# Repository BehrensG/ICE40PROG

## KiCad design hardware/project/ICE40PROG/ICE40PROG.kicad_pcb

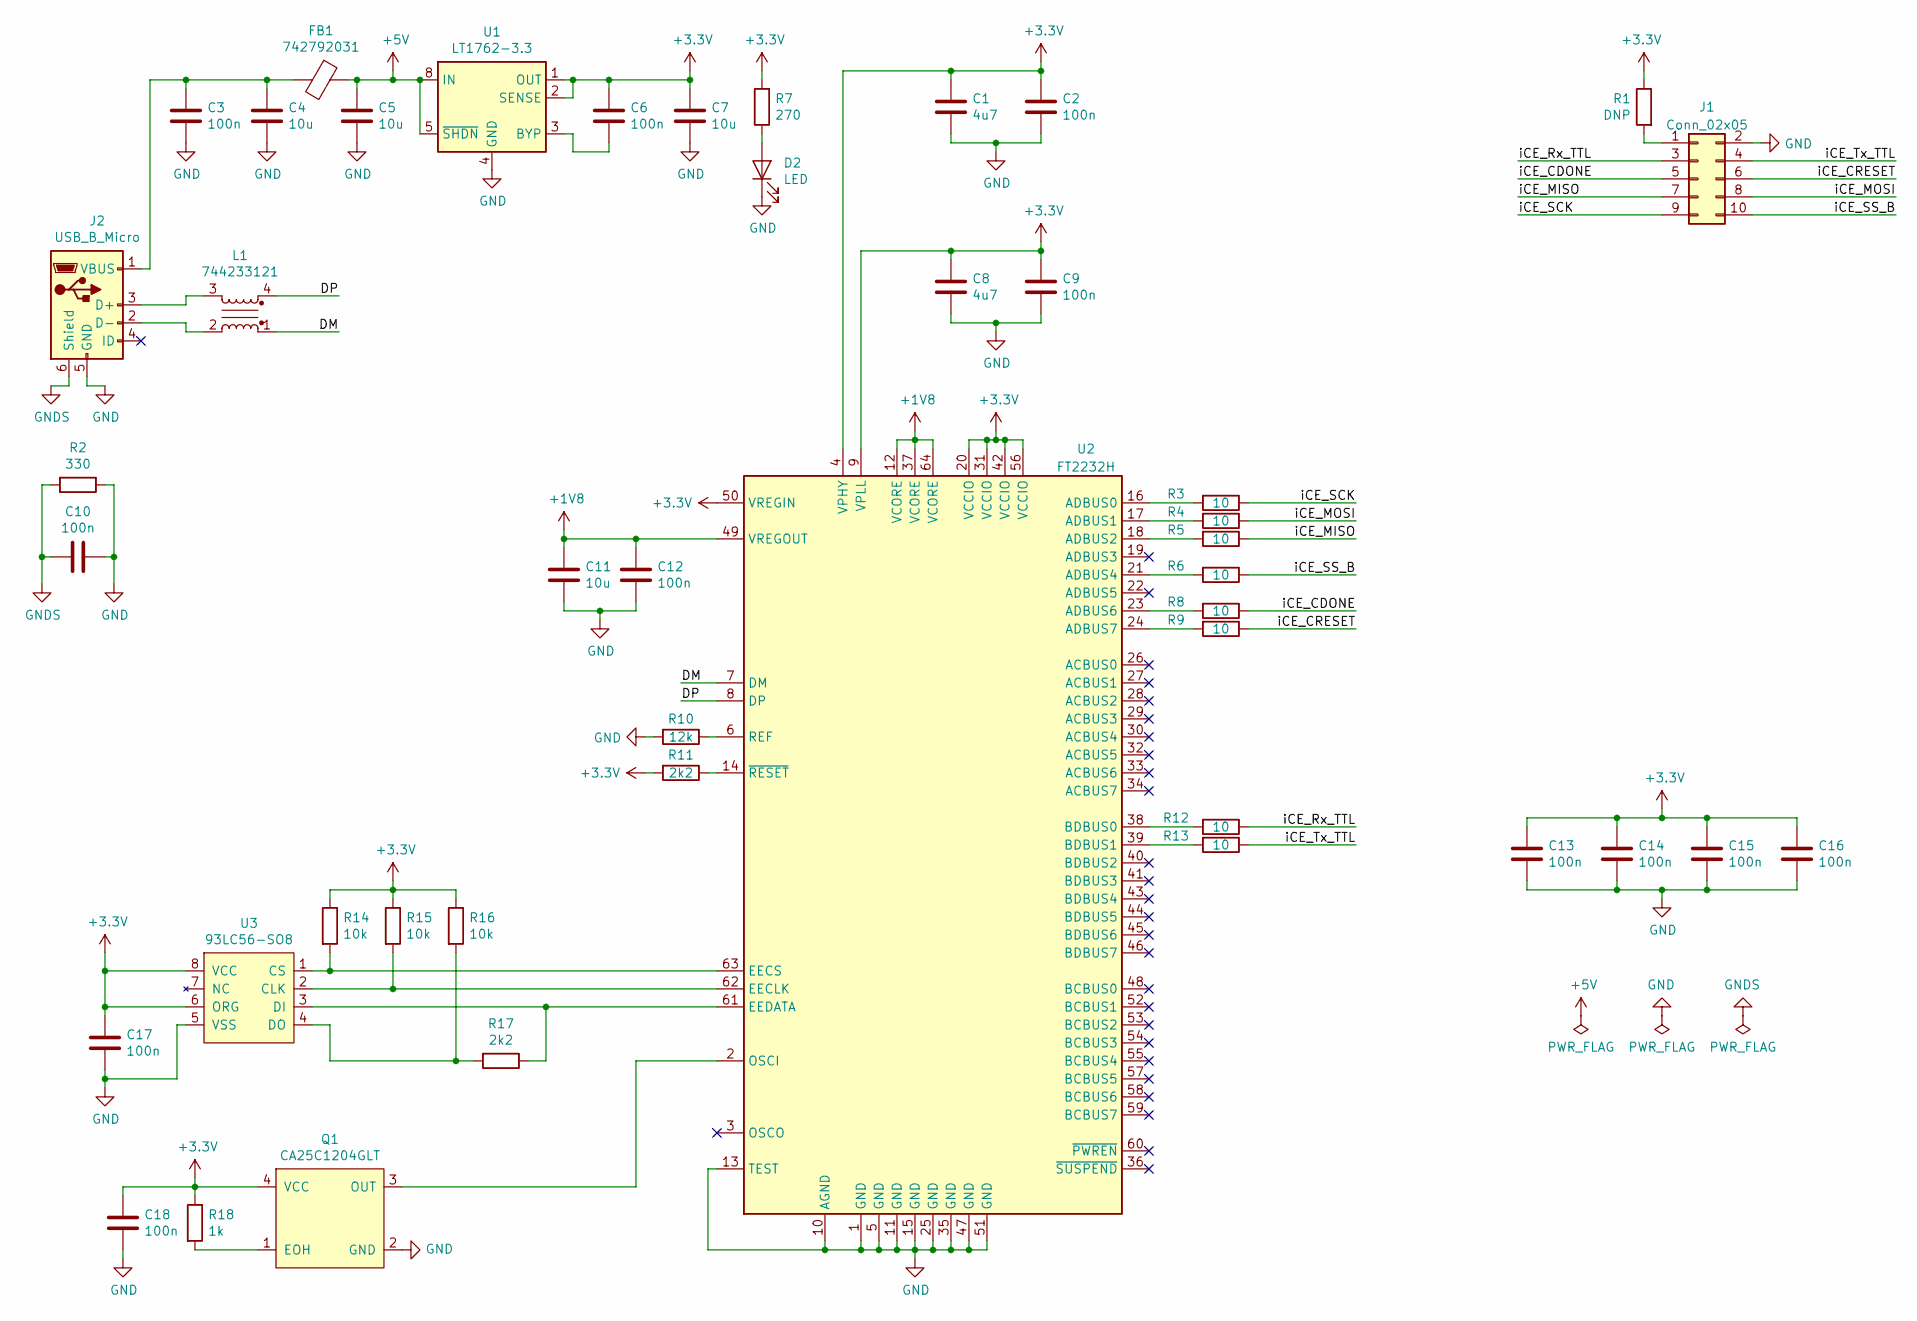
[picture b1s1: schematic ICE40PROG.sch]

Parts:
C1, C8: 4u7; C_0603_1608Metric_Pad1.05x0.95mm_HandSolder
C2, C3, C6, C9, C10, C12, C13, C14, C15, C16, C17, C18: 100n; C_0603_1608Metric_Pad1.05x0.95mm_HandSolder
C4, C5, C7, C11: 10u; C_0603_1608Metric_Pad1.05x0.95mm_HandSolder
D2: LED; LED_0603_1608Metric_Pad1.05x0.95mm_HandSolder
FB1: 742792031; R_0805_2012Metric_Pad1.15x1.40mm_HandSolder
J1: Conn_02x05; PinSocket_2x05_P2.54mm_Vertical
J2: USB_B_Micro; USB_Micro-B_Wuerth_629105150521
L1: 744233121
Q1: CA25C1204GLT; CA25
R1: DNP; R_0603_1608Metric_Pad1.05x0.95mm_HandSolder
R2: 330; R_0603_1608Metric_Pad1.05x0.95mm_HandSolder
R3, R4, R5, R6, R8, R9, R12, R13: 10; R_0603_1608Metric_Pad1.05x0.95mm_HandSolder
R7: 270; R_0603_1608Metric_Pad1.05x0.95mm_HandSolder
R10: 12k; R_0603_1608Metric_Pad1.05x0.95mm_HandSolder
R11, R17: 2k2; R_0603_1608Metric_Pad1.05x0.95mm_HandSolder
R14, R15, R16: 10k; R_0603_1608Metric_Pad1.05x0.95mm_HandSolder
R18: 1k; R_0603_1608Metric_Pad1.05x0.95mm_HandSolder
U1: LT1762-3.3; MSOP-8_3x3mm_P0.65mm
U2: FT2232H; LQFP-64_10x10mm_P0.5mm
U3: 93LC56-SO8; SOIC-8_3.9x4.9mm_P1.27mm

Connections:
+1V8: C11.1, C12.1, U2.12 (VCORE), U2.37 (VCORE), U2.49 (VREGOUT), U2.64 (VCORE)
+3V3: C1.1, C2.1, C6.1, C7.1, C8.1, C9.1, C13.1, C14.1, C15.1, C16.1, C17.1, C18.1, Q1.4 (VCC), R1.1, R7.2, R11.2, R14.1, R15.1, R16.1, R18.1, U1.1 (OUT), U1.2 (SENSE), U2.4 (VPHY), U2.9 (VPLL), U2.20 (VCCIO), U2.31 (VCCIO), U2.42 (VCCIO), U2.50 (VREGIN), U2.56 (VCCIO), U3.6 (ORG), U3.8 (VCC)
+5V: C5.1, FB1.1, U1.5 (~SHDN), U1.8 (IN)
/DM: L1.1, U2.7 (DM)
/DP: L1.4, U2.8 (DP)
/iCE_CDONE: J1.5, R8.1
/iCE_CRESET: J1.6, R9.1
/iCE_MISO: J1.7, R5.1
/iCE_MOSI: J1.8, R4.1
/iCE_Rx_TTL: J1.3, R12.1
/iCE_SCK: J1.9, R3.1
/iCE_SS_B: J1.10, R6.1
/iCE_Tx_TTL: J1.4, R13.1
GND: C1.2, C2.2, C3.2, C4.2, C5.2, C7.2, C8.2, C9.2, C10.1, C11.2, C12.2, C13.2, C14.2, C15.2, C16.2, C17.2, C18.2, D2.1 (K), J1.2, J2.5 (GND), Q1.2 (GND), R2.1, R10.2, U1.4 (GND), U2.1 (GND), U2.5 (GND), U2.10 (AGND), U2.11 (GND), U2.13 (TEST), U2.15 (GND), U2.25 (GND), U2.35 (GND), U2.47 (GND), U2.51 (GND), U3.5 (VSS)
GNDS: C10.2, J2.6 (Shield), R2.2
unnamed: C3.1, C4.1, FB1.2, J2.1 (VBUS)
unnamed: C6.2, U1.3 (BYP)
unnamed: D2.2 (A), R7.1
unnamed: J1.1, R1.2
unnamed: J2.2 (D-), L1.2
unnamed: J2.3 (D+), L1.3
unnamed: Q1.1 (EOH), R18.2
unnamed: Q1.3 (OUT), U2.2 (OSCI)
unnamed: R3.2, U2.16 (ADBUS0)
unnamed: R4.2, U2.17 (ADBUS1)
unnamed: R5.2, U2.18 (ADBUS2)
unnamed: R6.2, U2.21 (ADBUS4)
unnamed: R8.2, U2.23 (ADBUS6)
unnamed: R9.2, U2.24 (ADBUS7)
unnamed: R10.1, U2.6 (REF)
unnamed: R11.1, U2.14 (~RESET)
unnamed: R12.2, U2.38 (BDBUS0)
unnamed: R13.2, U2.39 (BDBUS1)
unnamed: R14.2, U2.63 (EECS), U3.1 (CS)
unnamed: R15.2, U2.62 (EECLK), U3.2 (CLK)
unnamed: R16.2, R17.2, U3.4 (DO)
unnamed: R17.1, U2.61 (EEDATA), U3.3 (DI)

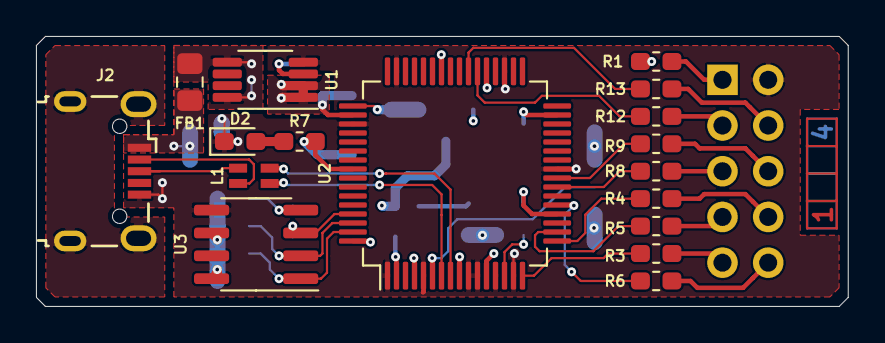
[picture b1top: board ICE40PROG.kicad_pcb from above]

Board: 4 copper layers, 45.1 x 15.0 mm, 45 parts (0 on the bottom side), 37 nets.

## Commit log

2020-02-07 PCB and schematic design
2020-02-08 Schematic, PCB and BOM done.
